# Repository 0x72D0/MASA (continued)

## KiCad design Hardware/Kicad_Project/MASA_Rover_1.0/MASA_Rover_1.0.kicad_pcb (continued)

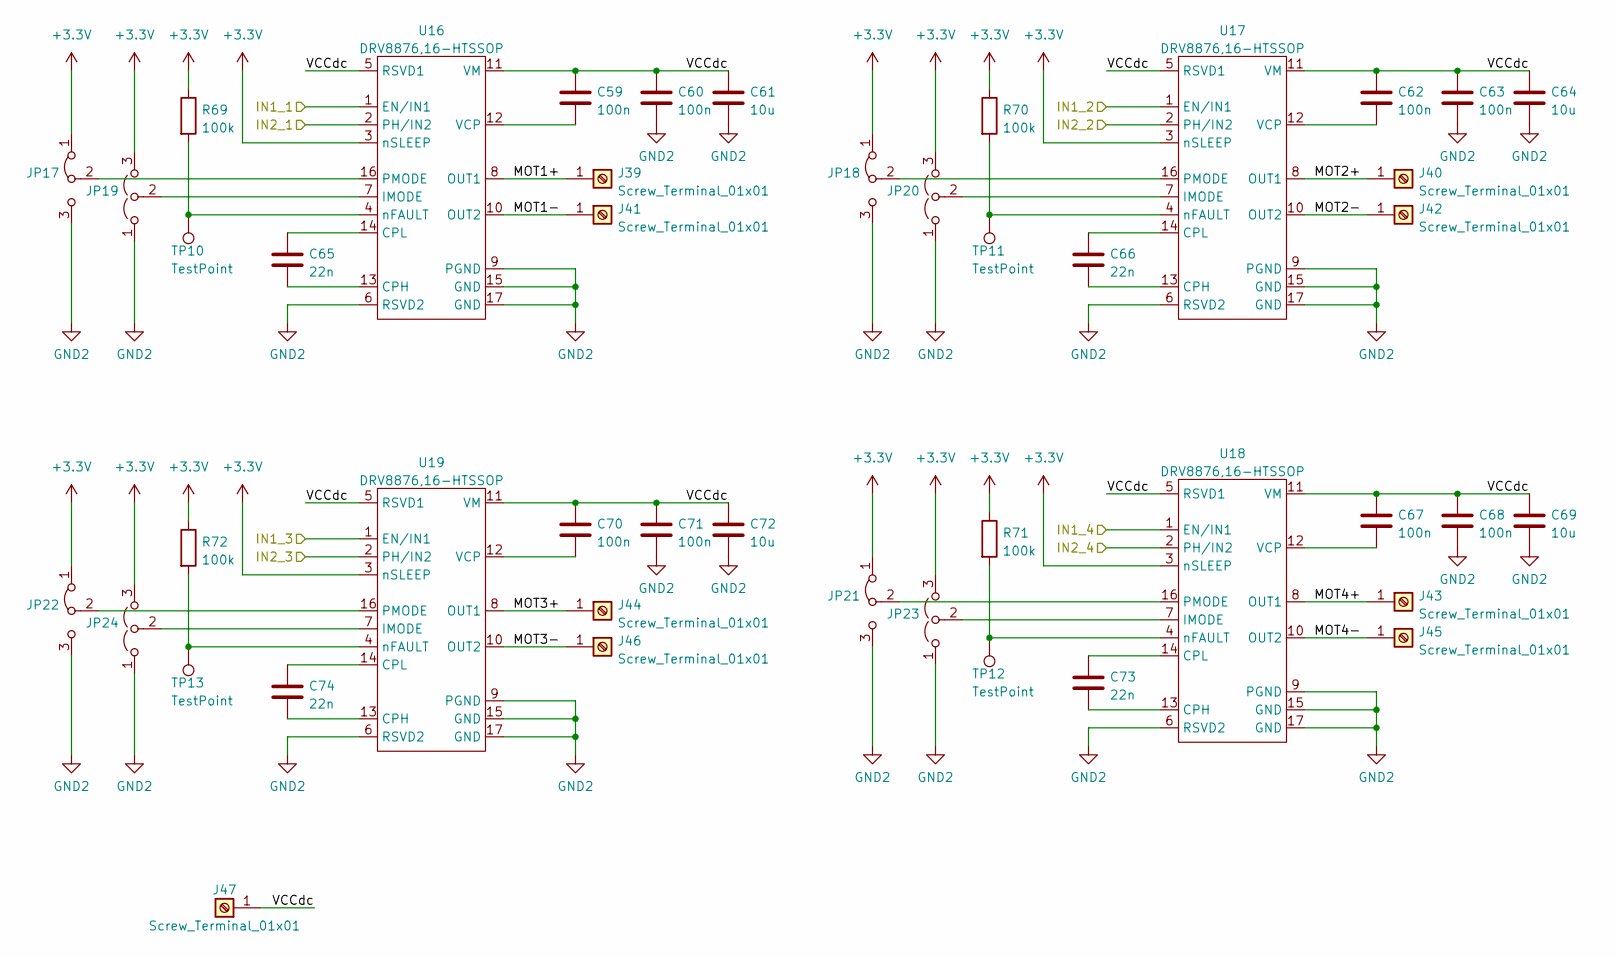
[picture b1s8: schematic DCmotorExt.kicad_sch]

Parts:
C59, C60, C62, C63, C67, C68, C70, C71: 100n; C_0805_2012Metric_Pad1.18x1.45mm_HandSolder
C61, C64, C69, C72: 10u; C_0805_2012Metric_Pad1.18x1.45mm_HandSolder
C65, C66, C73, C74: 22n; C_0805_2012Metric_Pad1.18x1.45mm_HandSolder
J39, J40, J41, J42, J43, J44, J45, J46, J47: Screw_Terminal_01x01; ScrewTerminal_1x01_5x7mm
JP17, JP18, JP21, JP22: Jumper_3_Bridged12; SolderJumper-3_P1.3mm_Bridged12_Pad1.0x1.5mm
JP19, JP20, JP23, JP24: Jumper_3_Open; SolderJumper-3_P1.3mm_Open_Pad1.0x1.5mm
R69, R70, R71, R72: 100k; R_0805_2012Metric_Pad1.20x1.40mm_HandSolder
TP10, TP11, TP12, TP13: TestPoint; TestPoint_Pad_D2.0mm
U16, U17, U18, U19: DRV8876,16-HTSSOP; HTSSOP-16-1EP_4.4x5mm_P0.65mm_EP3.4x5mm

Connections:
+3.3V: JP17.1 (A), JP18.1 (A), JP19.3 (B), JP20.3 (B), JP21.1 (A), JP22.1 (A), JP23.3 (B), JP24.3 (B), R69.1, R70.1, R71.1, R72.1, U16.3 (nSLEEP), U17.3 (nSLEEP), U18.3 (nSLEEP), U19.3 (nSLEEP); also elsewhere on the board
/Rover Extension/DC Motor Ext./MOT1+: J39.1, U16.8 (OUT1)
/Rover Extension/DC Motor Ext./MOT1-: J41.1, U16.10 (OUT2)
/Rover Extension/DC Motor Ext./MOT2+: J40.1, U17.8 (OUT1)
/Rover Extension/DC Motor Ext./MOT2-: J42.1, U17.10 (OUT2)
/Rover Extension/DC Motor Ext./MOT3+: J44.1, U19.8 (OUT1)
/Rover Extension/DC Motor Ext./MOT3-: J46.1, U19.10 (OUT2)
/Rover Extension/DC Motor Ext./MOT4+: J43.1, U18.8 (OUT1)
/Rover Extension/DC Motor Ext./MOT4-: J45.1, U18.10 (OUT2)
/Rover Extension/DC Motor Ext./VCCdc: C59.1, C60.1, C61.1, C62.1, C63.1, C64.1, C67.1, C68.1, C69.1, C70.1, C71.1, C72.1, J47.1, U16.5 (RSVD1), U16.11 (VM), U17.5 (RSVD1), U17.11 (VM), U18.5 (RSVD1), U18.11 (VM), U19.5 (RSVD1), U19.11 (VM)
/Rover Extension/PWM0: U16.1 (EN/IN1); also elsewhere on the board
/Rover Extension/PWM1: U16.2 (PH/IN2); also elsewhere on the board
/Rover Extension/PWM2: U17.1 (EN/IN1); also elsewhere on the board
/Rover Extension/PWM3: U17.2 (PH/IN2); also elsewhere on the board
/Rover Extension/PWM4: U19.1 (EN/IN1); also elsewhere on the board
/Rover Extension/PWM5: U19.2 (PH/IN2); also elsewhere on the board
/Rover Extension/PWM6: U18.1 (EN/IN1); also elsewhere on the board
/Rover Extension/PWM7: U18.2 (PH/IN2); also elsewhere on the board
GND2: C60.2, C61.2, C63.2, C64.2, C68.2, C69.2, C71.2, C72.2, JP17.3 (B), JP18.3 (B), JP19.1 (A), JP20.1 (A), JP21.3 (B), JP22.3 (B), JP23.1 (A), JP24.1 (A), U16.6 (RSVD2), U16.9 (PGND), U16.15 (GND), U16.17 (GND), U17.6 (RSVD2), U17.9 (PGND), U17.15 (GND), U17.17 (GND), U18.6 (RSVD2), U18.9 (PGND), U18.15 (GND), U18.17 (GND), U19.6 (RSVD2), U19.9 (PGND), U19.15 (GND), U19.17 (GND); also elsewhere on the board
unnamed: C59.2, U16.12 (VCP)
unnamed: C62.2, U17.12 (VCP)
unnamed: C65.1, U16.14 (CPL)
unnamed: C65.2, U16.13 (CPH)
unnamed: C66.1, U17.14 (CPL)
unnamed: C66.2, U17.13 (CPH)
unnamed: C67.2, U18.12 (VCP)
unnamed: C70.2, U19.12 (VCP)
unnamed: C73.1, U18.14 (CPL)
unnamed: C73.2, U18.13 (CPH)
unnamed: C74.1, U19.14 (CPL)
unnamed: C74.2, U19.13 (CPH)
unnamed: JP17.2 (C), U16.16 (PMODE)
unnamed: JP18.2 (C), U17.16 (PMODE)
unnamed: JP19.2 (C), U16.7 (IMODE)
unnamed: JP20.2 (C), U17.7 (IMODE)
unnamed: JP21.2 (C), U18.16 (PMODE)
unnamed: JP22.2 (C), U19.16 (PMODE)
unnamed: JP23.2 (C), U18.7 (IMODE)
unnamed: JP24.2 (C), U19.7 (IMODE)
unnamed: R69.2, TP10.1, U16.4 (nFAULT)
unnamed: R70.2, TP11.1, U17.4 (nFAULT)
unnamed: R71.2, TP12.1, U18.4 (nFAULT)
unnamed: R72.2, TP13.1, U19.4 (nFAULT)

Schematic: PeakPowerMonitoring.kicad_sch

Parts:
C27, C28: 100n; C_0805_2012Metric_Pad1.18x1.45mm_HandSolder
C29: 1u; C_0805_2012Metric_Pad1.18x1.45mm_HandSolder
C30: 4.7u; C_0805_2012Metric_Pad1.18x1.45mm_HandSolder
J8, J9, J10, J11: Screw_Terminal_01x01; ScrewTerminal_1x01_5x7mm
Q2: BC847BS; SOT-363_SC-70-6
Q3: IRLML0060TRPBF; SOT-23
R18, R19: 0R01; R_2512_6332Metric_Pad1.40x3.35mm_HandSolder
R20: 270k; R_0805_2012Metric_Pad1.20x1.40mm_HandSolder
R21, R22, R28, R29: 1k; R_0805_2012Metric_Pad1.20x1.40mm_HandSolder
R23: 30k; R_0805_2012Metric_Pad1.20x1.40mm_HandSolder
R24, R25: 33k; R_0805_2012Metric_Pad1.20x1.40mm_HandSolder
R26, R27: 200; R_0805_2012Metric_Pad1.20x1.40mm_HandSolder
R30: 1M; R_0805_2012Metric_Pad1.20x1.40mm_HandSolder
R31: 10k; R_0805_2012Metric_Pad1.20x1.40mm_HandSolder
U7, U8: LTC6102HVxMS8; MSOP-8_3x3mm_P0.65mm
U9: LTC6247,8-TSSOP; TSSOP-8_3x3mm_P0.65mm

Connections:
+3V3: C29.2, R26.1, R27.1, R31.1, U9.8 (V+); also elsewhere on the board
/I2C Expenders/AIN0: R20.2, R23.1; also elsewhere on the board
/I2C Expenders/AIN1: R24.2, U7.4 (OUT); also elsewhere on the board
/I2C Expenders/AIN2: U9.6 (-INB), U9.7 (OUTB); also elsewhere on the board
/I2C Expenders/IO0_5: Q3.1 (G), R31.2; also elsewhere on the board
/I2C Expenders/Peak Power Monitoring/PPM_Entry: J8.1, R18.1, R20.1, R21.2
GND: C29.1, C30.1, J10.1, J11.1, Q3.2 (S), R23.2, R24.1, R25.1, R28.2, R30.2, U7.3 (V-), U7.5 (V-), U8.3 (V-), U8.5 (V-), U9.4 (V-); also elsewhere on the board
unnamed: C27.1, U7.6 (VREG)
unnamed: C27.2, R18.2, R19.1, R22.2, U7.7 (V+), U7.8 (+IN)
unnamed: C28.1, U8.6 (VREG)
unnamed: C28.2, J9.1, R19.2, U8.7 (V+), U8.8 (+IN)
unnamed: C30.2, Q2.4 (E2), Q3.3 (D), R30.1, U9.5 (+INB)
unnamed: Q2.1 (E1), R28.1, U9.2 (-INA)
unnamed: Q2.2 (B1), Q2.5 (B2), U9.1 (OUTA)
unnamed: Q2.3 (C2), R27.2
unnamed: Q2.6 (C1), R26.2
unnamed: R21.1, U7.1 (-INS), U7.2 (-INF)
unnamed: R22.1, U8.1 (-INS), U8.2 (-INF)
unnamed: R25.2, R29.2, U8.4 (OUT)
unnamed: R29.1, U9.3 (+INA)

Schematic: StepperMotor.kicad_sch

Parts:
A1, A2: Pololu_Breakout_DRV8825; Pololu_Breakout-16_15.2x20.3mm
J26, J27: Conn_01x04_Male; PinHeader_1x04_P2.54mm_Vertical
J28, J29: Screw_Terminal_01x01; ScrewTerminal_1x01_5x7mm
R52, R53: R; R_0805_2012Metric_Pad1.20x1.40mm_HandSolder

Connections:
/I2C Expenders/AIN5: R52.2, R53.1; also elsewhere on the board
/I2C Expenders/IO0_0: A1.15 (STEP); also elsewhere on the board
/I2C Expenders/IO0_1: A1.16 (DIR); also elsewhere on the board
/I2C Expenders/IO0_2: A1.10 (M0); also elsewhere on the board
/I2C Expenders/IO0_3: A1.11 (M1); also elsewhere on the board
/I2C Expenders/IO0_4: A1.12 (M2); also elsewhere on the board
/I2C Expenders/IO1_0: A2.15 (STEP); also elsewhere on the board
/I2C Expenders/IO1_1: A2.16 (DIR); also elsewhere on the board
/I2C Expenders/IO1_2: A2.10 (M0); also elsewhere on the board
/I2C Expenders/IO1_3: A2.11 (M1); also elsewhere on the board
/I2C Expenders/IO1_4: A2.12 (M2); also elsewhere on the board
/I2C Expenders/Stepper Motor/A1_1: A1.4 (A1), J26.2
/I2C Expenders/Stepper Motor/A1_2: A2.4 (A1), J27.2
/I2C Expenders/Stepper Motor/A2_1: A1.3 (A2), J26.1
/I2C Expenders/Stepper Motor/A2_2: A2.3 (A2), J27.1
/I2C Expenders/Stepper Motor/B1_1: A1.5 (B1), J26.3
/I2C Expenders/Stepper Motor/B1_2: A2.5 (B1), J27.3
/I2C Expenders/Stepper Motor/B2_1: A1.6 (B2), J26.4
/I2C Expenders/Stepper Motor/B2_2: A2.6 (B2), J27.4
/I2C Expenders/Stepper Motor/VCCstp: A1.8 (VMOT), A2.8 (VMOT), J28.1, R52.1
GND: A1.1 (GND), A1.7 (GND), A1.9 (~EN), A1.13 (~RST), A1.14 (~SLP), A2.1 (GND), A2.7 (GND), A2.9 (~EN), A2.13 (~RST), A2.14 (~SLP), J29.1, R53.2; also elsewhere on the board

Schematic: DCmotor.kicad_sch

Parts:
C35, C36, C38, C39, C43, C44, C46, C47: 100n; C_0805_2012Metric_Pad1.18x1.45mm_HandSolder
C37, C40, C45, C48: 10u; C_0805_2012Metric_Pad1.18x1.45mm_HandSolder
C41, C42, C49, C50: 22n; C_0805_2012Metric_Pad1.18x1.45mm_HandSolder
J16, J17, J18, J19, J20, J21, J22, J23, J24, J25: Screw_Terminal_01x01; ScrewTerminal_1x01_5x7mm
JP5, JP6, JP9, JP10: Jumper_3_Bridged12; SolderJumper-3_P1.3mm_Bridged12_Pad1.0x1.5mm
JP7, JP8, JP11, JP12: Jumper_3_Open; SolderJumper-3_P1.3mm_Open_Pad1.0x1.5mm
R46, R47, R48, R49: 100k; R_0805_2012Metric_Pad1.20x1.40mm_HandSolder
R50, R51: R; R_0805_2012Metric_Pad1.20x1.40mm_HandSolder
TP6, TP7, TP8, TP9: TestPoint; TestPoint_Pad_D2.0mm
U10, U11, U12, U13: DRV8876,16-HTSSOP; HTSSOP-16-1EP_4.4x5mm_P0.65mm_EP3.4x5mm

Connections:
+5V: JP5.1 (A), JP6.1 (A), JP7.3 (B), JP8.3 (B), JP9.1 (A), JP10.1 (A), JP11.3 (B), JP12.3 (B), R46.1, R47.1, R48.1, R49.1, U10.3 (nSLEEP), U11.3 (nSLEEP), U12.3 (nSLEEP), U13.3 (nSLEEP); also elsewhere on the board
/I2C Expenders/AIN4: R50.2, R51.1; also elsewhere on the board
/I2C Expenders/DC Motor/MOT1+: J16.1, U10.8 (OUT1)
/I2C Expenders/DC Motor/MOT1-: J18.1, U10.10 (OUT2)
/I2C Expenders/DC Motor/MOT2+: J17.1, U11.8 (OUT1)
/I2C Expenders/DC Motor/MOT2-: J19.1, U11.10 (OUT2)
/I2C Expenders/DC Motor/MOT3+: J21.1, U13.8 (OUT1)
/I2C Expenders/DC Motor/MOT3-: J23.1, U13.10 (OUT2)
/I2C Expenders/DC Motor/MOT4+: J20.1, U12.8 (OUT1)
/I2C Expenders/DC Motor/MOT4-: J22.1, U12.10 (OUT2)
/I2C Expenders/DC Motor/VCCdc: C35.1, C36.1, C37.1, C38.1, C39.1, C40.1, C43.1, C44.1, C45.1, C46.1, C47.1, C48.1, J24.1, R50.1, U10.5 (RSVD1), U10.11 (VM), U11.5 (RSVD1), U11.11 (VM), U12.5 (RSVD1), U12.11 (VM), U13.5 (RSVD1), U13.11 (VM)
/I2C Expenders/PWM0: U10.1 (EN/IN1); also elsewhere on the board
/I2C Expenders/PWM1: U10.2 (PH/IN2); also elsewhere on the board
/I2C Expenders/PWM2: U11.1 (EN/IN1); also elsewhere on the board
/I2C Expenders/PWM3: U11.2 (PH/IN2); also elsewhere on the board
/I2C Expenders/PWM4: U13.1 (EN/IN1); also elsewhere on the board
/I2C Expenders/PWM5: U13.2 (PH/IN2); also elsewhere on the board
/I2C Expenders/PWM6: U12.1 (EN/IN1); also elsewhere on the board
/I2C Expenders/PWM7: U12.2 (PH/IN2); also elsewhere on the board
GND: C36.2, C37.2, C39.2, C40.2, C44.2, C45.2, C47.2, C48.2, J25.1, JP5.3 (B), JP6.3 (B), JP7.1 (A), JP8.1 (A), JP9.3 (B), JP10.3 (B), JP11.1 (A), JP12.1 (A), R51.2, U10.6 (RSVD2), U10.9 (PGND), U10.15 (GND), U10.17 (GND), U11.6 (RSVD2), U11.9 (PGND), U11.15 (GND), U11.17 (GND), U12.6 (RSVD2), U12.9 (PGND), U12.15 (GND), U12.17 (GND), U13.6 (RSVD2), U13.9 (PGND), U13.15 (GND), U13.17 (GND); also elsewhere on the board
unnamed: C35.2, U10.12 (VCP)
unnamed: C38.2, U11.12 (VCP)
unnamed: C41.1, U10.14 (CPL)
unnamed: C41.2, U10.13 (CPH)
unnamed: C42.1, U11.14 (CPL)
unnamed: C42.2, U11.13 (CPH)
unnamed: C43.2, U12.12 (VCP)
unnamed: C46.2, U13.12 (VCP)
unnamed: C49.1, U12.14 (CPL)
unnamed: C49.2, U12.13 (CPH)
unnamed: C50.1, U13.14 (CPL)
unnamed: C50.2, U13.13 (CPH)
unnamed: JP5.2 (C), U10.16 (PMODE)
unnamed: JP6.2 (C), U11.16 (PMODE)
unnamed: JP7.2 (C), U10.7 (IMODE)
unnamed: JP8.2 (C), U11.7 (IMODE)
unnamed: JP9.2 (C), U12.16 (PMODE)
unnamed: JP10.2 (C), U13.16 (PMODE)
unnamed: JP11.2 (C), U12.7 (IMODE)
unnamed: JP12.2 (C), U13.7 (IMODE)
unnamed: R46.2, TP6.1, U10.4 (nFAULT)
unnamed: R47.2, TP7.1, U11.4 (nFAULT)
unnamed: R48.2, TP8.1, U12.4 (nFAULT)
unnamed: R49.2, TP9.1, U13.4 (nFAULT)

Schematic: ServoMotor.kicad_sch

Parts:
C31, C32, C33, C34: 1u; C_0805_2012Metric_Pad1.18x1.45mm_HandSolder
J12, J13, J14, J15: Conn_01x03_Male; PinHeader_1x03_P2.54mm_Vertical
Q4, Q5, Q6, Q7, Q8, Q9, Q10, Q11: T2N7002; SOT-23
R32, R35, R38, R41: 100k; R_0805_2012Metric_Pad1.20x1.40mm_HandSolder
R33, R34, R36, R37, R39, R40, R42, R45: 10k; R_0805_2012Metric_Pad1.20x1.40mm_HandSolder
R43, R44: R; R_0805_2012Metric_Pad1.20x1.40mm_HandSolder

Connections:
+5V: C31.1, C32.1, C33.1, C34.1, J12.2, J13.2, J14.2, J15.2, R32.1, R33.1, R35.1, R36.1, R38.1, R39.1, R41.1, R42.1, R43.1; also elsewhere on the board
/I2C Expenders/AIN3: R43.2, R44.1; also elsewhere on the board
/I2C Expenders/PWM8: Q4.1 (G), R34.1; also elsewhere on the board
/I2C Expenders/PWM9: Q6.1 (G), R37.1; also elsewhere on the board
/I2C Expenders/PWM10: Q8.1 (G), R40.1; also elsewhere on the board
/I2C Expenders/PWM11: Q10.1 (G), R45.1; also elsewhere on the board
GND: C31.2, C32.2, C33.2, C34.2, J12.3, J13.3, J14.3, J15.3, Q4.2 (S), Q5.2 (S), Q6.2 (S), Q7.2 (S), Q8.2 (S), Q9.2 (S), Q10.2 (S), Q11.2 (S), R34.2, R37.2, R40.2, R44.2, R45.2; also elsewhere on the board
unnamed: J12.1, Q5.3 (D), R33.2
unnamed: J13.1, Q7.3 (D), R36.2
unnamed: J14.1, Q9.3 (D), R39.2
unnamed: J15.1, Q11.3 (D), R42.2
unnamed: Q4.3 (D), Q5.1 (G), R32.2
unnamed: Q6.3 (D), Q7.1 (G), R35.2
unnamed: Q8.3 (D), Q9.1 (G), R38.2
unnamed: Q10.3 (D), Q11.1 (G), R41.2

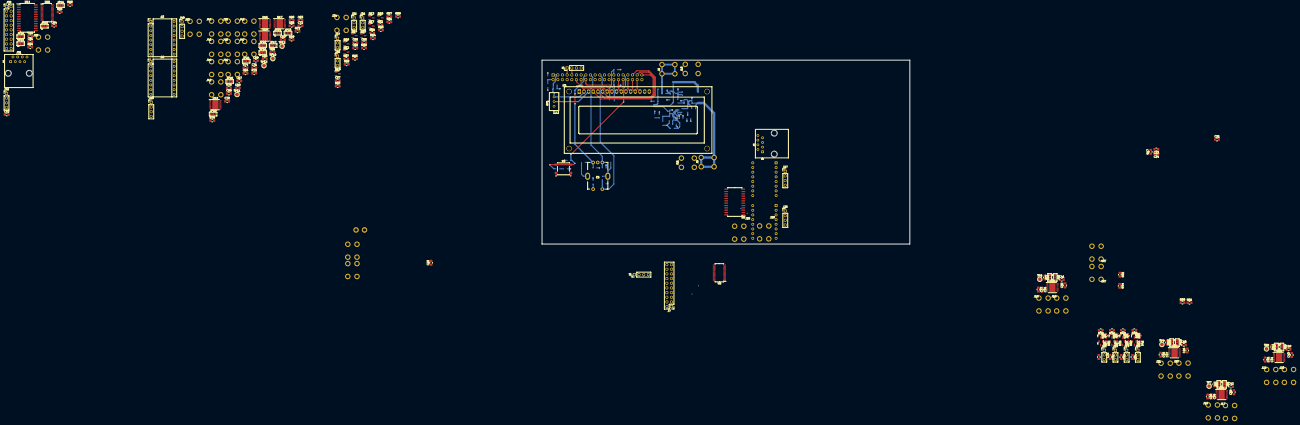
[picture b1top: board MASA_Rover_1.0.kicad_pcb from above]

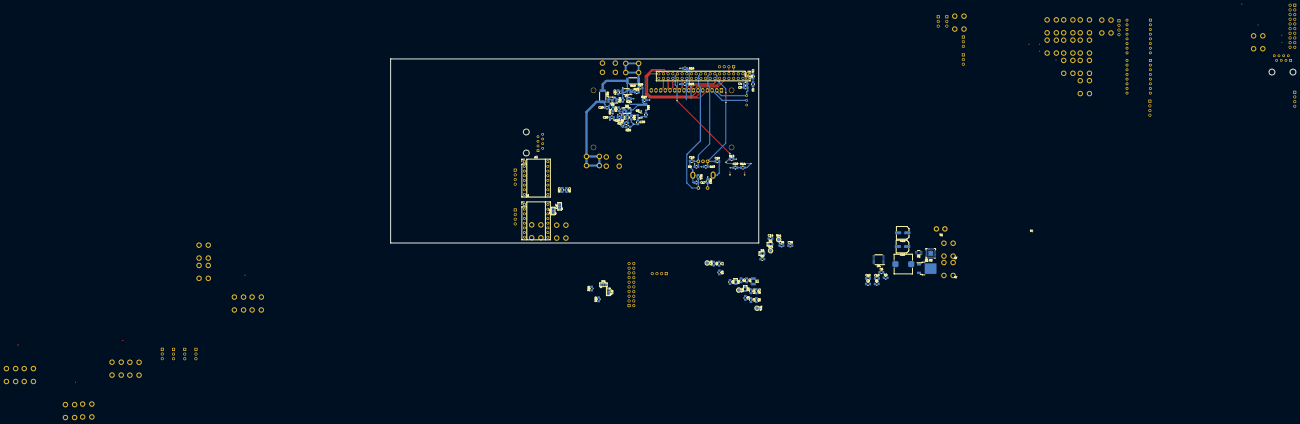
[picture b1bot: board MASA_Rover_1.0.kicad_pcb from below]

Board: 4 copper layers, 200.0 x 100.0 mm, 288 parts (91 on the bottom side), 238 nets.

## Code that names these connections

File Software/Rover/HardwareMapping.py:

from Model.Component import Component, ComponentType
from View.PCA9535View import PCA9535Config
from View.PCA9685View import PCA9685Config

# contains all pinout definition

ROTARY_ENCODER_D2_PIN=40
ROTARY_ENCODER_D3_PIN=38
ROTARY_ENCODER_SW_PIN=19

BACK_BUTTON_PIN=23

LCD_RS_PIN=22 # on the board it's RW
LCD_E_PIN=18 # on the board it's RS
#LCD_RW_PIN=36 # on the board it's E

LCD_D0_PIN=11
LCD_D1_PIN=13
LCD_D2_PIN=15
LCD_D3_PIN=12

# contains I2C addressing

PCA_0_PORT = 0x01
PCA_0_ADDR = 0x70

PCA_1_PORT = 0x01
PCA_1_ADDR = 0x20

# contains PCA9685 configuration

PCA_0_CONFIG = [
    PCA9685Config([9, 8], Component(ComponentType.DC_MOTOR, 0)),
    PCA9685Config([11, 10], Component(ComponentType.DC_MOTOR, 1)),
    PCA9685Config([13, 12], Component(ComponentType.DC_MOTOR, 2)),
    PCA9685Config([15, 14], Component(ComponentType.DC_MOTOR, 3)),
    PCA9685Config([4], Component(ComponentType.SERVO_MOTOR, 0)), 
    PCA9685Config([5], Component(ComponentType.SERVO_MOTOR, 1)), 
    PCA9685Config([6], Component(ComponentType.SERVO_MOTOR, 2)), 
    PCA9685Config([7], Component(ComponentType.SERVO_MOTOR, 3))
    ]

PCA_1_CONFIG = [
    PCA9535Config([11, 12, 8, 9, 10], Component(ComponentType.STEPPER, 0)),
    PCA9535Config([1, 0, 4, 3, 2], Component(ComponentType.STEPPER, 1)),
    ]

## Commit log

2022-09-21 move graphical menu into the model
2022-09-21 add profile to the model
2022-09-25 change the project architecture
2022-09-26 add a little test
2022-09-26 add Viewer and Controller
2022-09-26 separate Software and hardware
2022-09-29 lcd addons
2022-10-02 improve lcd
2022-10-05 making the servo work
2022-10-05 adding rotary encoder repo (temporary)
2022-10-08 implement the profile and mapping
2022-10-11 Menu handling refactoring
2022-10-11 rework the lcd list handling
2022-10-11 fix button bug
2022-10-14 add profile menu
2022-10-15 write custom mapping
2022-10-15 add comment to each class
2022-10-16 implement all the profile logic, except the profile naming
2022-10-17 finish polishing the profile menu
2022-10-18 dabble implemented
2022-10-20 implement stepping and release
2022-11-05 add hardware
2022-11-12 add analogic input
2022-11-12 add temporary dummy motor
2022-11-12 add choose component menu
2022-11-12 adding profile options
2022-11-13 add monitoring
2022-11-25 refactoring control system
2022-11-28 refactor PCA9685 and specify list type
2022-11-28 continu motor implementation
2022-12-03 officially add stepper and DC
2022-12-04 adding mapping for final product
2022-12-11 bringup test 1
2022-12-12 bring up 2
2022-12-14 bringup 3
2022-12-14 update hardware
2022-12-14 add first modelio diagram
